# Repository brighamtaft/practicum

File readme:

(411RoughDraft.brd, 411RoughtDraft.sch) - status: complete - the 411roughDraft (.brd and .sch) are the original design files for our device. They are messy and error prone and do not hold any merit in the final design

(BOM.-Sheet1.pdf) - status: incomplete - Bill of Materials - has the appropriate quantity and compnents necessary for the PCB population but has yet to include the necessary materials needed for the container.

(BOM_Finalrev.xsl) - status complete - Bill of Materilas - up to date includes all necessary compoenents to be purchased.

(BankCode_rev1) - status: complete - The first complete rev for the arduino code used. Edit this to change the function of the microprocessor

(Child’s Piggy Bank.pptx) - status: incomplete - Presentation for final project that has in detail on what we did step by step 

(CointControllerV1.brd, CointControllerV1.sch) - status: complete - The complete schematic and brd layout for the device. Send the .brd file in to be printed.

(Coin Sort Face v5.stl, Coin Sort Ramp v5.stl) - status: complete but untested. These files have the same dimensions as the laser cut acrylic sorter and should work but have not been 3d printed and tested.

(TestPlan.pdf) - status: assignment comp[lete - test documentation with descriptions. Minimal test case in accordance with the assignment.

(Coin Sorter (Sized) v1.f3d) - status: complete but untested. This is a working 3D CAD file for fusion 360. It has been optimized to use minimum material and fit in a small print bed. It will require extensive supports to print with SLA style printer and would be recommended to split at the intersection of the ramp before printing in that style 3D printer.

(Design.pdf) - status: complete - basic block diagram of the basic functions of our device

(NextLevelDesign.pdf) - status: complete - a more detailed diagram of the functionality of our device

(PDS.docx) - status: complete - Product Design Specifications document

(ProjectBrainstorming.docx, Top.3.Ideas.docx) - status: complete - record of the project ideas for our group

(preliminarySchematicIMG.jfif, preliminarySchematic.sch) - status: complete - the very first incomplete basic schematic of device

(prototype.jpg) - status: complete - the first implemented device using buttons instead of sensors and an arduino

(testProcedure.docx) - status: incomplete - document describing the test procedure for the device

(T17 HW7 Test Plan.pdf) - status: complete - Homework based test plan.

(BetterSortV2.dxf) - status: Complete - Laser Printable file for acrylic coin sorter. Known to work with cast acrylic but not tested on other materials.

Programming instruction:
1) Flash the arduino bootloader onto the atmega328p. This can be done following the online tutorial found in this link: https://www.arduino.cc/en/Tutorial/ArduinoToBreadboard
2) Once the bootloader has been flashed you can solder the atmega328p to the board or insert it into a sleeve if you chose to purchase one.
3) Once the entire board is populated you can program the atmega328p with the BankCode_rev1 code. This can be done following the tutorial found at the same link as burning the bootloader. The difference in the connections is described below

Connections: (remember to remove the atmega328p from the arduinouno before programming)
  1) Arduino TX pin connects to pin5 of the 6x1 pin header
  2) Arduino RX pin connects to pin4 of the 6x1 pin header
  3) Arduino Vcc pin connects to pin2 of the 3x2 pin header
  4) Arduino gnd pin connects to pin6 of the 3x2 pin header
  5) Arduino reset pin connects to pin5 of the 3x2 pin header
  
 4) Once the wiring has been done upload the CoinCollector code to arduino as you normally would with the board selected being Arduino nano (atmega328p processor selected).
 5) The board should be ready to be wired up to the LCD screen and sensors. And you can begin the test procedure (see testProcedure.docx)

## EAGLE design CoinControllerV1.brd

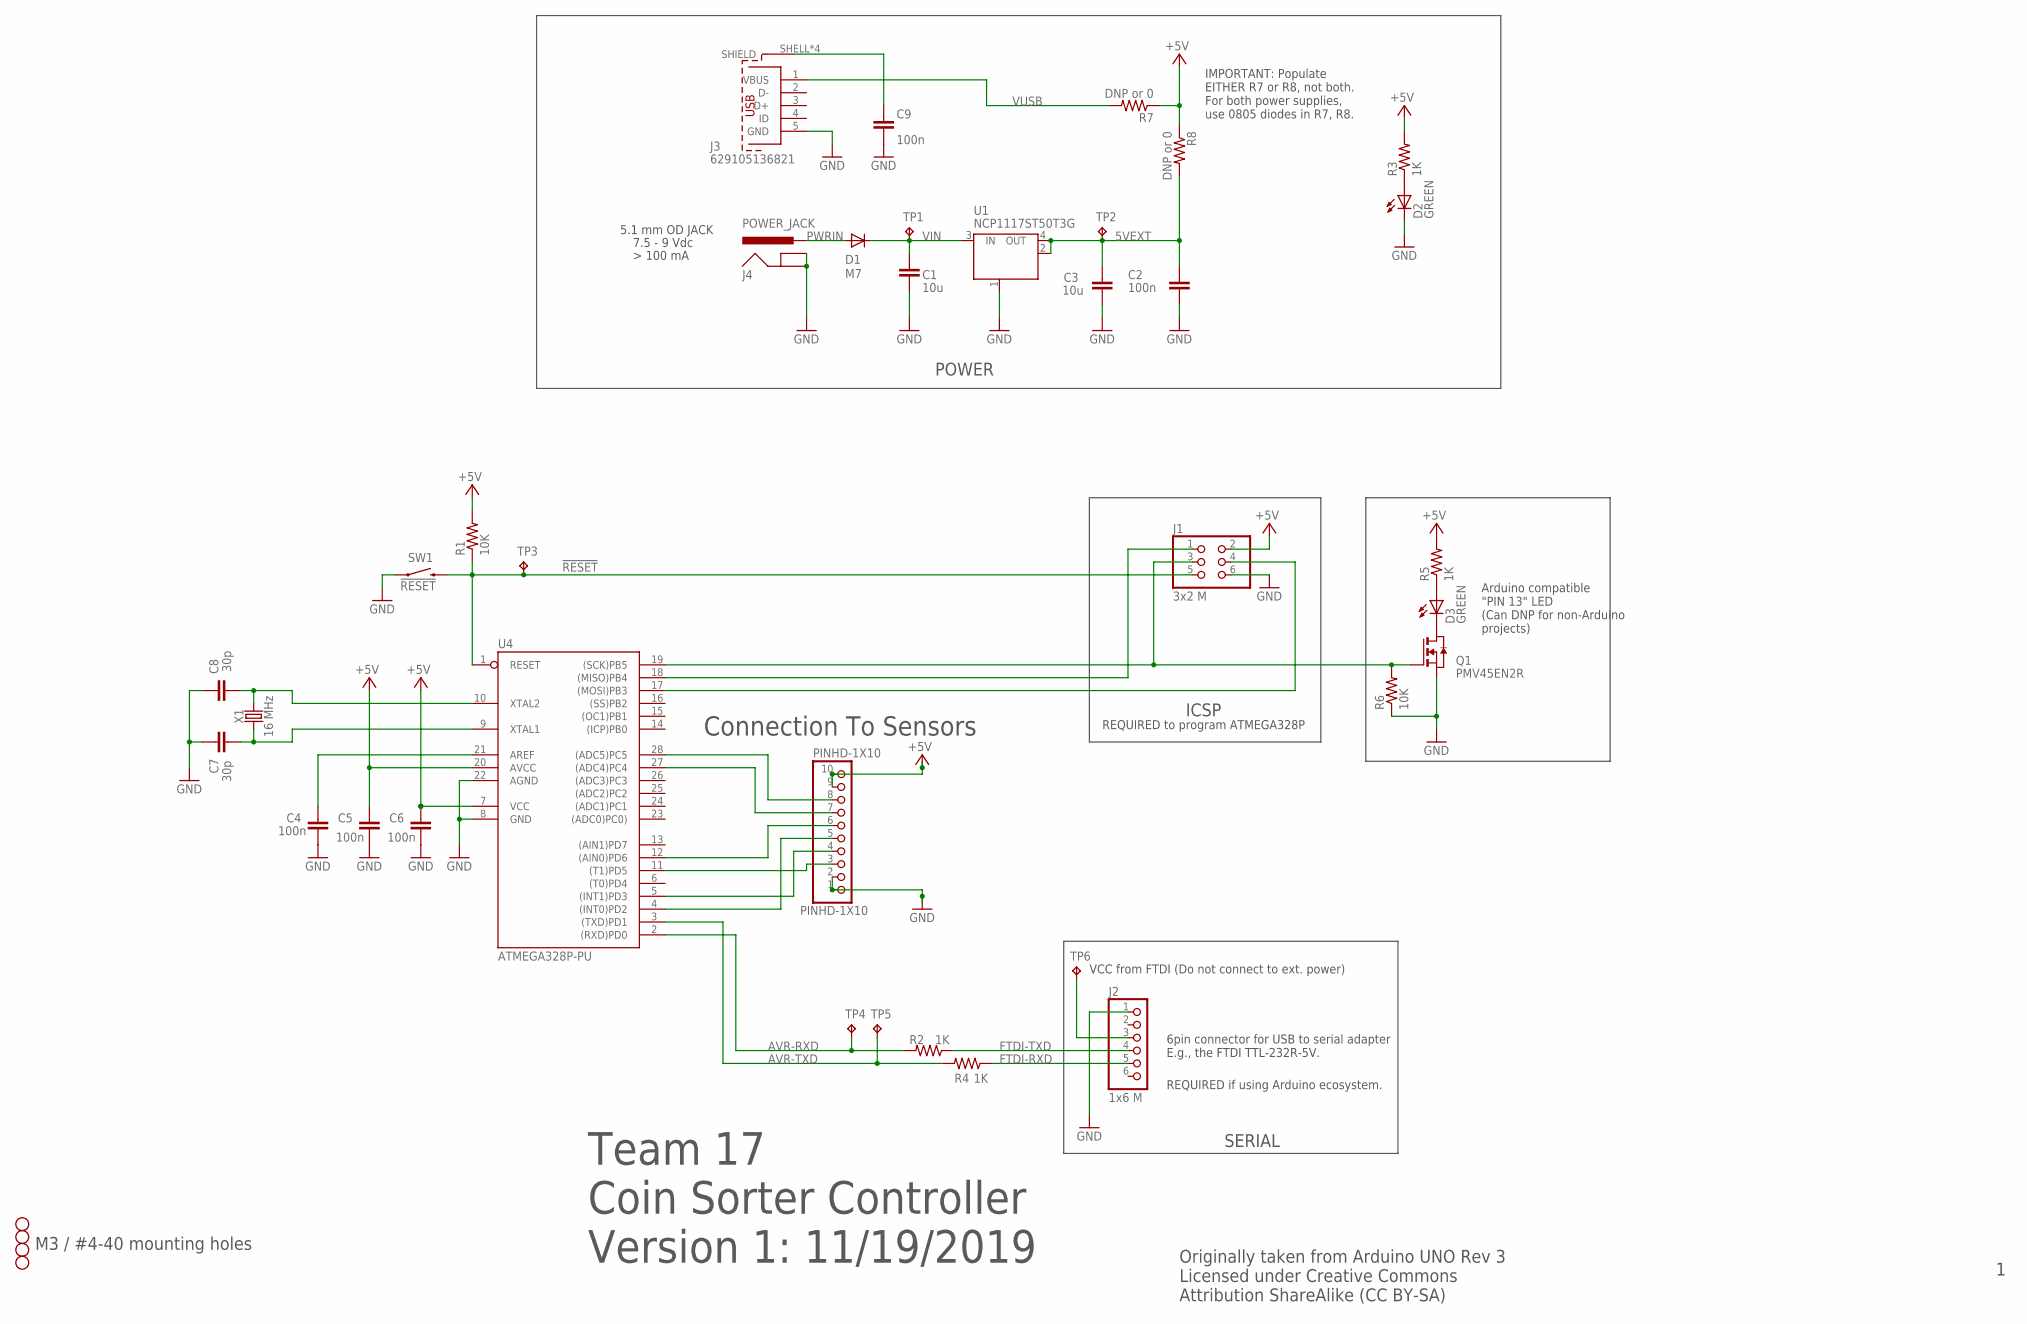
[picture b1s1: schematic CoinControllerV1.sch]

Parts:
C1, C3: 10u; C0805K; MPN CL21A106KOQNNNG
C2, C4, C5, C6, C9: 100n; C0805K; MPN CL21B104KBCNNNC
C7: 30p; C0805K; MPN CL21C180JBANNNC
C8: 30p; C0805K; MPN CL21C300JBANNNC
D1: M7; SMB; MPN 10BQ030TR
D2, D3: GREEN; CHIP-LED0805; MPN 150080GS75000
H1, H2, H3, H4: STAND-OFF
J1: 3x2 M; 2X03; MPN M20-9980345
J2: 1x6 M; 1X06; MPN PRPC006SAAN-RC
J3: 629105136821; MPN 629105136821
J4: POWER_JACK; POWER_JACK_PTH; MPN PJ-202A
PINHD-1X10: PINHD-1X10; 1X10-BIG
Q1: PMV45EN2R; SOT-23; MPN PMV45EN2R
R1, R6: 10K; R0805; MPN RC0805FR-0710KL
R2, R3, R4, R5: 1K; R0805; MPN RC0805FR-071KL
R7, R8: DNP or 0; R0805; MPN RC0805JR-070RL
SW1: !RESET; TACTILE_SWITCH_SMD; MPN RS-187R05A2-DS MT RT
TP1, TP2, TP3, TP4, TP5, TP6: TPPAD1-13; P1-13
U1: NCP1117ST50T3G; SOT223; MPN NCP1117ST50T3G
U4: ATMEGA328P-PU; DIL28-3; MPN ATMEGA328P-PU
X1: 16 MHz; HC49UP; MPN ECS-160-18-5PX-TR

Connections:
5VEXT: C2.2, C3.1, R8.2, TP2.TP, U1.2 (OUT), U1.4 (OUT)
!RESET: J1.5, R1.1, SW1.3 (2), TP3.TP, U4.1 (RESET)
+5V: C5.2, C6.2, J1.2, PINHD-1X10.9, PINHD-1X10.10, R1.2, R3.2, R5.2, R7.1, R8.1, U4.7 (VCC), U4.20 (AVCC)
AVR-RXD: R2.2, TP4.TP, U4.2 ((RXD)PD0)
AVR-TXD: R4.2, TP5.TP, U4.3 ((TXD)PD1)
FTDI-RXD: J2.5, R4.1
FTDI-TXD: J2.4, R2.1
GND: C1.2, C2.1, C3.2, C4.1, C5.1, C6.1, C7.2, C8.2, C9.1, D2.C, J1.6, J2.1, J3.5 (GND), J4.GND, J4.GNDBREAK, PINHD-1X10.1, PINHD-1X10.2, Q1.2 (S), R6.1, SW1.1, U1.1 (GND/ADJ), U4.8 (GND), U4.22 (AGND)
MISO: J1.1, U4.18 ((MISO)PB4)
MOSI: J1.4, U4.17 ((MOSI)PB3)
unnamed: C4.2, U4.21 (AREF)
unnamed: D3.A, R5.1
unnamed: D2.A, R3.1
unnamed: D3.C, Q1.1 (D)
unnamed: J2.3, TP6.TP
unnamed: C9.2, J3.SHELL (SHIELD), J3.SHELL1 (SHIELD), J3.SHELL2 (SHIELD), J3.SHELL3 (SHIELD)
unnamed: PINHD-1X10.5, U4.4 ((INT0)PD2)
unnamed: PINHD-1X10.4, U4.5 ((INT1)PD3)
unnamed: PINHD-1X10.3, U4.11 ((T1)PD5)
unnamed: PINHD-1X10.6, U4.12 ((AIN0)PD6)
unnamed: PINHD-1X10.7, U4.27 ((ADC4)PC4)
unnamed: PINHD-1X10.8, U4.28 ((ADC5)PC5)
PWRIN: D1.A, J4.PWR
SCK: J1.3, Q1.3 (G), R6.2, U4.19 ((SCK)PB5)
VIN: C1.1, D1.C, TP1.TP, U1.3 (IN)
VUSB: J3.1 (VBUS), R7.2
XTAL1: C7.1, U4.9 (XTAL1), X1.1
XTAL2: C8.1, U4.10 (XTAL2), X1.2

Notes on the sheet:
7.5 - 9 Vdc
POWER
ICSP
5.1 mm OD JACK
6pin connector for USB to serial adapter E.g., the FTDI TTL-232R-5V.
REQUIRED if using Arduino ecosystem.
M3 / #4-40 mounting holes
SERIAL
REQUIRED to program ATMEGA328P
Arduino compatible "PIN 13" LED (Can DNP for non-Arduino projects)
VCC from FTDI (Do not connect to ext. power)
IMPORTANT: Populate EITHER R7 or R8, not both. For both power supplies, use 0805 diodes in R7, R8.
Originally taken from Arduino UNO Rev 3 Licensed under Creative Commons Attribution ShareAlike (CC BY-SA)
Team 17 Coin Sorter Controller Version 1: 11/19/2019
Connection To Sensors

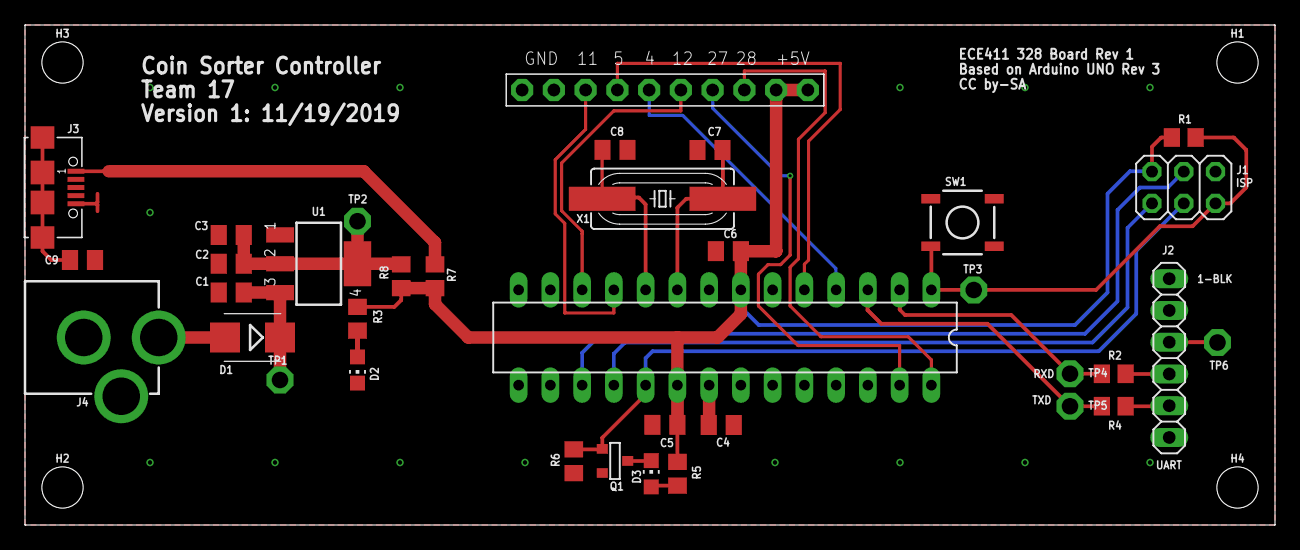
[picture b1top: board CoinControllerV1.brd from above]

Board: 2 copper layers, 100.0 x 40.0 mm, 40 parts (0 on the bottom side), 28 nets.

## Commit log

2019-10-10 Create practicumIdeas
2019-10-10 Create ProjectIdeas
2019-10-17 Create Top3Ideas
2019-10-27 Create BankCode_rev1
2019-12-07 Create CAD
    Storage for Fusion 360 Files, DXF files for laser printing, EMF files for laser Cutting and .stl files for 3d Printing.

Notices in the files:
parts and their libraries:
SparkFun-Connectors: Licensing: Creative Commons ShareAlike 4.0 International - https://creativecommons.org/licenses/by-sa/4.0
Wurth_Elektronik_Electromechanic_Input-O: Copyright: Würth Elektronik
